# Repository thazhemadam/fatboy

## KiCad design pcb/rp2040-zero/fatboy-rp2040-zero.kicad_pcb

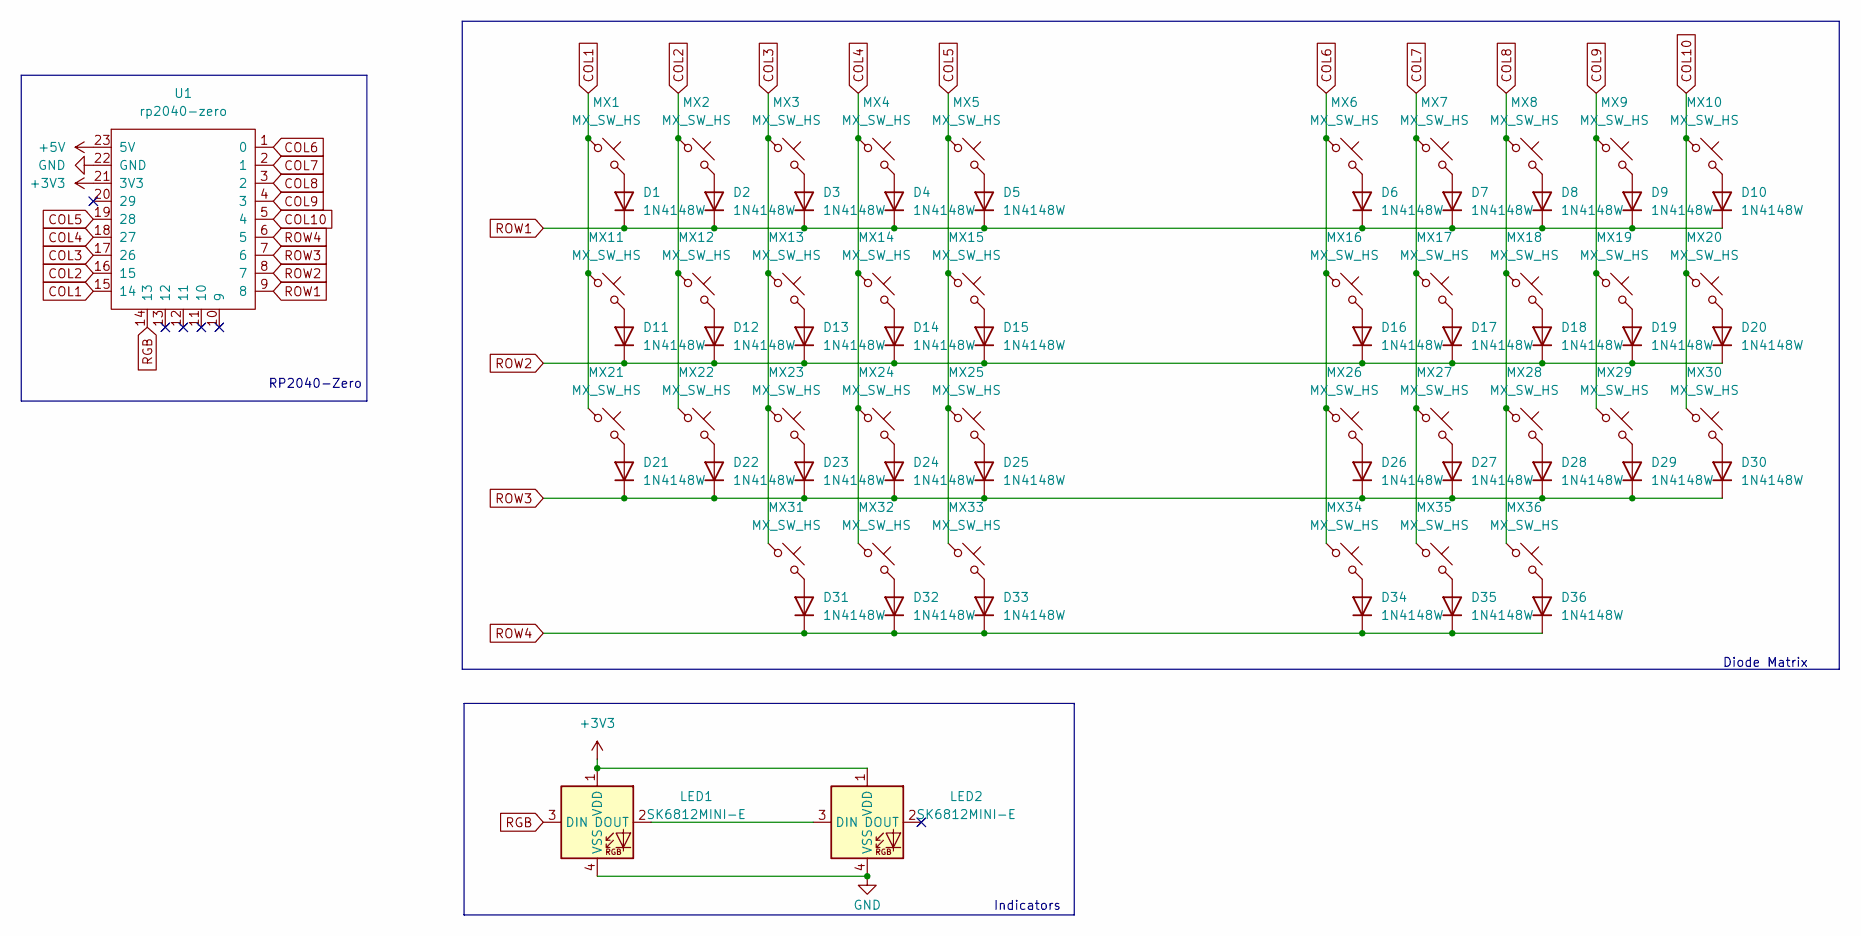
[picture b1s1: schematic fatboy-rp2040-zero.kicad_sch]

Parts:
D1, D2, D3, D4, D5, D6, D7, D8, D9, D10, D11, D12, D13, D14, D15, D16, D17, D18, D19, D20, D21, D22, D23, D24, D25, D26, D27, D28, D29, D30, D31, D32, D33, D34, D35, D36: 1N4148W; D_SOD-123
LED1, LED2: SK6812MINI-E; LED_6028R
MX1, MX2, MX3, MX4, MX5, MX6, MX7, MX8, MX9, MX10, MX11, MX12, MX13, MX14, MX15, MX16, MX17, MX18, MX19, MX20, MX21, MX22, MX23, MX24, MX25, MX26, MX27, MX28, MX29, MX30, MX31, MX32, MX33, MX34, MX35, MX36: MX_SW_HS; SW_MX_HS_CPG151101S11_1u
U1: rp2040-zero; rp2040-zero-tht

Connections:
+3V3: LED1.1 (VDD), LED2.1 (VDD), U1.21 (3V3)
+5V: U1.23 (5V)
COL1: MX1.1, MX11.1, MX21.1, U1.15 (14)
COL2: MX2.1, MX12.1, MX22.1, U1.16 (15)
COL3: MX3.1, MX13.1, MX23.1, MX31.1, U1.17 (26)
COL4: MX4.1, MX14.1, MX24.1, MX32.1, U1.18 (27)
COL5: MX5.1, MX15.1, MX25.1, MX33.1, U1.19 (28)
COL6: MX6.1, MX16.1, MX26.1, MX34.1, U1.1 (0)
COL7: MX7.1, MX17.1, MX27.1, MX35.1, U1.2 (1)
COL8: MX8.1, MX18.1, MX28.1, MX36.1, U1.3 (2)
COL9: MX9.1, MX19.1, MX29.1, U1.4 (3)
COL10: MX10.1, MX20.1, MX30.1, U1.5 (4)
GND: LED1.4 (VSS), LED2.4 (VSS), U1.22 (GND)
unnamed: D1.2 (A), MX1.2
unnamed: D2.2 (A), MX2.2
unnamed: D3.2 (A), MX3.2
unnamed: D4.2 (A), MX4.2
unnamed: D5.2 (A), MX5.2
unnamed: D6.2 (A), MX6.2
unnamed: D7.2 (A), MX7.2
unnamed: D8.2 (A), MX8.2
unnamed: D9.2 (A), MX9.2
unnamed: D10.2 (A), MX10.2
unnamed: D11.2 (A), MX11.2
unnamed: D12.2 (A), MX12.2
unnamed: D13.2 (A), MX13.2
unnamed: D14.2 (A), MX14.2
unnamed: D15.2 (A), MX15.2
unnamed: D16.2 (A), MX16.2
unnamed: D17.2 (A), MX17.2
unnamed: D18.2 (A), MX18.2
unnamed: D19.2 (A), MX19.2
unnamed: D20.2 (A), MX20.2
unnamed: D21.2 (A), MX21.2
unnamed: D22.2 (A), MX22.2
unnamed: D23.2 (A), MX23.2
unnamed: D24.2 (A), MX24.2
unnamed: D25.2 (A), MX25.2
unnamed: D26.2 (A), MX26.2
unnamed: D27.2 (A), MX27.2
unnamed: D28.2 (A), MX28.2
unnamed: D29.2 (A), MX29.2
unnamed: D30.2 (A), MX30.2
unnamed: D31.2 (A), MX31.2
unnamed: D32.2 (A), MX32.2
unnamed: D33.2 (A), MX33.2
unnamed: D34.2 (A), MX34.2
unnamed: D35.2 (A), MX35.2
unnamed: D36.2 (A), MX36.2
unnamed: LED1.2 (DOUT), LED2.3 (DIN)
RGB: LED1.3 (DIN), U1.14 (13)
ROW1: D1.1 (K), D2.1 (K), D3.1 (K), D4.1 (K), D5.1 (K), D6.1 (K), D7.1 (K), D8.1 (K), D9.1 (K), D10.1 (K), U1.9 (8)
ROW2: D11.1 (K), D12.1 (K), D13.1 (K), D14.1 (K), D15.1 (K), D16.1 (K), D17.1 (K), D18.1 (K), D19.1 (K), D20.1 (K), U1.8 (7)
ROW3: D21.1 (K), D22.1 (K), D23.1 (K), D24.1 (K), D25.1 (K), D26.1 (K), D27.1 (K), D28.1 (K), D29.1 (K), D30.1 (K), U1.7 (6)
ROW4: D31.1 (K), D32.1 (K), D33.1 (K), D34.1 (K), D35.1 (K), D36.1 (K), U1.6 (5)

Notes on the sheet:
RP2040-Zero
Indicators
Diode Matrix

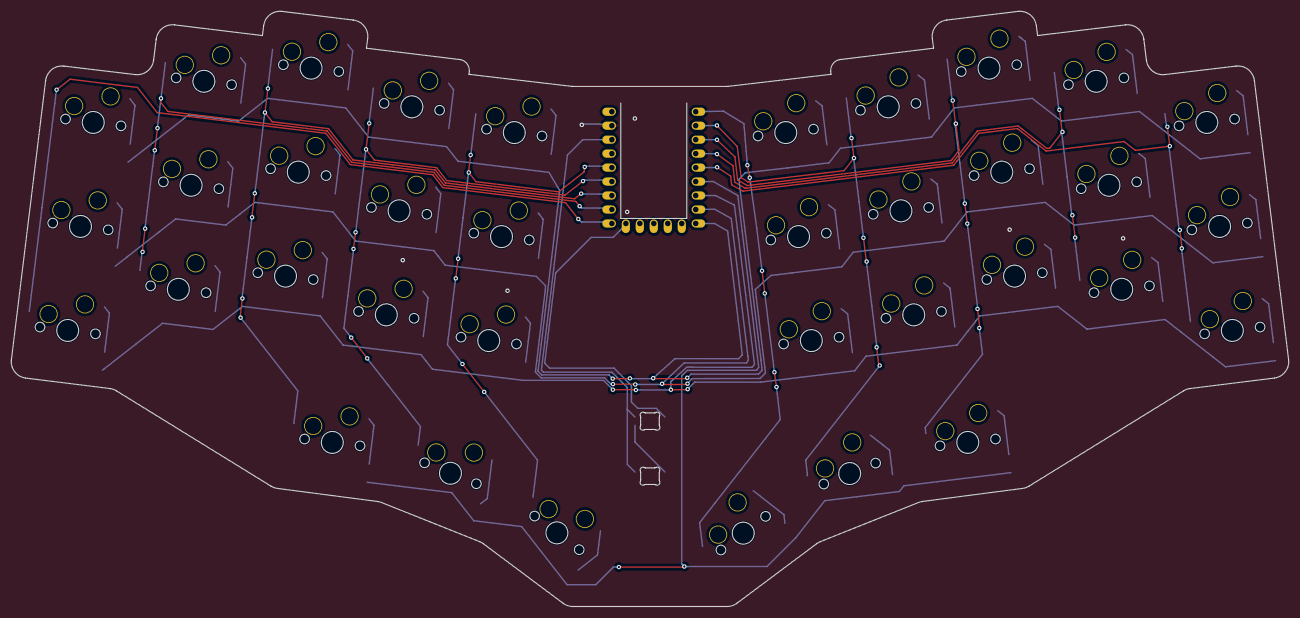
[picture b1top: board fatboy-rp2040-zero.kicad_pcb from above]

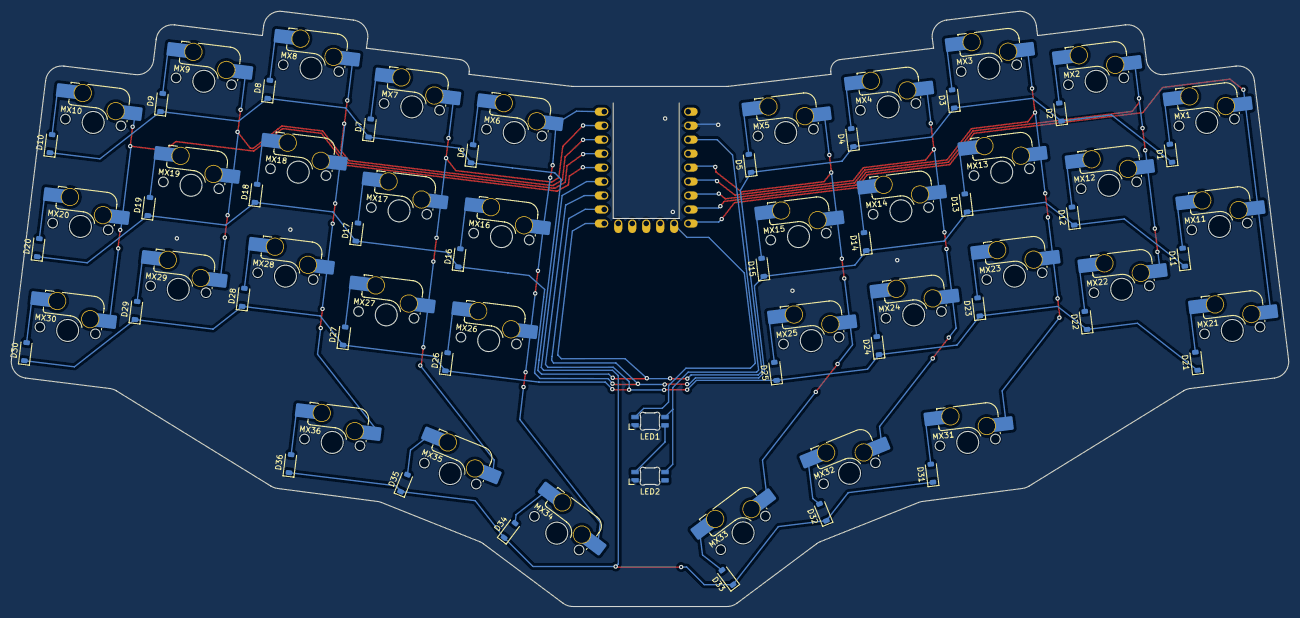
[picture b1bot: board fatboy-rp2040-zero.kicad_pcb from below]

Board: 2 copper layers, 232.2 x 108.2 mm, 75 parts (74 on the bottom side), 54 nets.

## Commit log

2024-03-15 pcb: remove jlcjlcjlcjlc on the back of pcb
2024-03-15 add .gitignore
2024-03-15 pcb: update to latest KiCad version by saving
2024-03-15 sch: update symbols from library
2024-03-15 plate: update to latest KiCad version by saving
2024-03-15 sch: remove extra led
2024-03-15 sch: remove daughterboard
2024-03-15 pcb: remove daughterboard
2024-03-15 pcb: update footprint from library
2024-03-15 update helios footprint
2024-03-15 update to use PCM_marbastlib:LED6028R
2024-03-15 helios: move over design files to `helios` directory
    Move over the project design files for the helios version to the
    `helios` directory.
2024-03-15 update reset switch footprint
2024-03-15 sch: update diode symbols
2024-03-15 pcb: remove `models`
2024-03-15 pcb(libs): add `marbastlib` as a submodule
2024-03-15 pcb: remove `gerbers`
2024-03-15 remove libs/marbastlib
2024-03-15 update MX HS SW footprint to PCM_marbastlib-mx:SW_MX_HS_CPG151101S11_1u
2024-03-15 pcb: move down LEDs
2024-03-15 remove fatboy.pretty
2024-03-15 pcb: remove extra led
2024-03-15 helios: rename `fatboy` to `fatboy-helios`
2024-03-15 helios: use `libs/marbastlib` for symbols and footprints
    Instead of implicitly relying on the assumption that the `marbastlib`
    (or any other library, really) will be present in development
    environment, expliciltly rely on the respective submodule version
    of the library
2024-03-15 move case, foam, plate folders into old, since they're no longer valid
2024-03-15 docs: update README
2024-03-15 ignore .lck files
2024-03-15 update footprints on pcb
2024-03-15 sch: reorder schematic a little
2024-03-15 libs: add kleeb lib
2024-03-15 rp2040-zero: copy over from helios
2024-03-15 sch: update symbol from helios to rp2040-zero
2024-03-15 reposition rows
2024-03-15 remove RST button
2024-03-15 rerouted rgb
2024-03-15 reroute rows
2024-03-15 fix routes
2024-03-15 rp2040-zero: add `rp2040-zero-facedown` footprint
2024-03-18 sch: replace global symbols with power symbols for power pins
2024-03-18 sch: add labels for shift register and MCU
2024-03-18 sch: remove RESET switch and rearrange LED
    Note: The RESET switch is removed since the RP2040-Zero doesn't have
    a pin for it anyways.
2024-03-19 rp2040-zero: finish up design
    * Move rows and column labels to digital pins instead of analog, since
    the latter has been reported to apparently have random issues with
    registering keypresses sometimes
    * Re-route tracks
    * Remove unnecessary labels
    * Remove shift register, since this will require a significant re-write
2024-03-19 rp2040-zero: fix DRC issues
